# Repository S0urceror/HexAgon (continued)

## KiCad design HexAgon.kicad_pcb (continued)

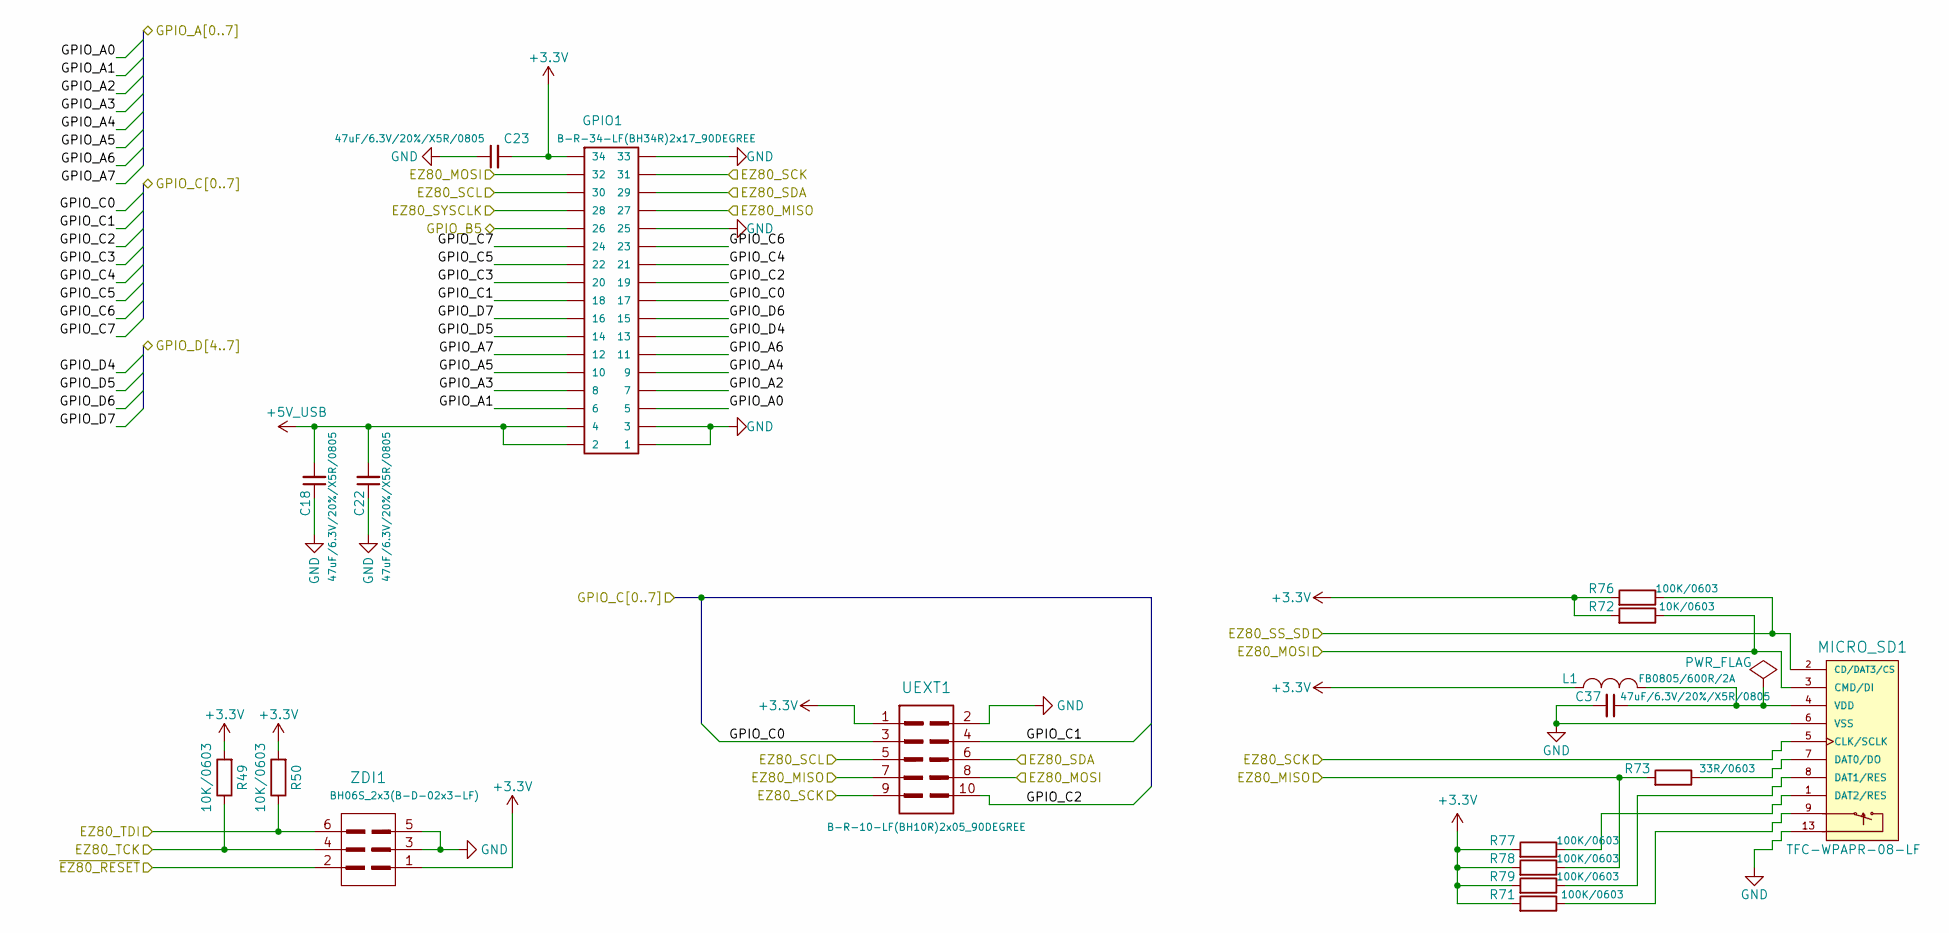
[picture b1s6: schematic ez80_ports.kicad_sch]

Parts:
C18, C22, C23, C37: 47uF/6.3V/20%/X5R/0805; C_0805_5MIL_DWS
GPIO1: B-R-34-LF(BH34R)2x17_90DEGREE; BH34R
L1: FB0805/600R/2A; L_0805_5MIL_DWS
MICRO_SD1: TFC-WPAPR-08-LF; TFC-WPAPR-08
R49, R50, R72: 10K/0603; R_0603_5MIL_DWS
R71, R76, R77, R78, R79: 100K/0603; R_0603_5MIL_DWS
R73: 33R/0603; R_0603_5MIL_DWS
UEXT1: B-R-10-LF(BH10R)2x05_90DEGREE; UEXT_BH10R
ZDI1: BH06S_2x3(B-D-02x3-LF); BH06S

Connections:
+3.3V: C23.2, GPIO1.34, L1.1, R49.2, R50.2, R71.2, R72.2, R76.2, R77.2, R78.2, R79.2, UEXT1.1, ZDI1.1; also elsewhere on the board
+5V_USB: C18.2, C22.2, GPIO1.2, GPIO1.4; also elsewhere on the board
/ESP32/ESP_SPI_MISO: GPIO1.27, R73.2, R78.1, UEXT1.7; also elsewhere on the board
/ESP32/ESP_SPI_MOSI: GPIO1.32, MICRO_SD1.3 (CMD/DI), R72.1, UEXT1.8; also elsewhere on the board
/ESP32/ESP_SPI_SCLK: GPIO1.31, MICRO_SD1.5 (CLK/SCLK), UEXT1.9; also elsewhere on the board
/EZ80 ports/EZ80_SCL: GPIO1.30, UEXT1.5; also elsewhere on the board
/EZ80 ports/EZ80_SDA: GPIO1.29, UEXT1.6; also elsewhere on the board
/EZ80 ports/EZ80_SS_SD: MICRO_SD1.2 (CD/DAT3/CS), R76.1; also elsewhere on the board
/EZ80 ports/EZ80_TCK: R49.1, ZDI1.4; also elsewhere on the board
/EZ80 ports/EZ80_TDI: R50.1, ZDI1.6; also elsewhere on the board
/EZ80 ports/GPIO_B5: GPIO1.26; also elsewhere on the board
/EZ80/CLOCK: GPIO1.28; also elsewhere on the board
/EZ80/PA0: GPIO1.5; also elsewhere on the board
/EZ80/PA1: GPIO1.6; also elsewhere on the board
/EZ80/PA2: GPIO1.7; also elsewhere on the board
/EZ80/PA3: GPIO1.8; also elsewhere on the board
/EZ80/PA4: GPIO1.9; also elsewhere on the board
/EZ80/PA5: GPIO1.10; also elsewhere on the board
/EZ80/PA6: GPIO1.11; also elsewhere on the board
/EZ80/PA7: GPIO1.12; also elsewhere on the board
/EZ80/PC0: GPIO1.17, UEXT1.3; also elsewhere on the board
/EZ80/PC1: GPIO1.18, UEXT1.4; also elsewhere on the board
/EZ80/PC2: GPIO1.19, UEXT1.10; also elsewhere on the board
/EZ80/PC3: GPIO1.20; also elsewhere on the board
/EZ80/PC4: GPIO1.21; also elsewhere on the board
/EZ80/PC5: GPIO1.22; also elsewhere on the board
/EZ80/PC6: GPIO1.23; also elsewhere on the board
/EZ80/PC7: GPIO1.24; also elsewhere on the board
/EZ80/PD4: GPIO1.13; also elsewhere on the board
/EZ80/PD5: GPIO1.14; also elsewhere on the board
/EZ80/PD6: GPIO1.15; also elsewhere on the board
/EZ80/PD7: GPIO1.16; also elsewhere on the board
/EZ80/~RESET: ZDI1.2; also elsewhere on the board
GND: C18.1, C22.1, C23.1, C37.2, GPIO1.1, GPIO1.3, GPIO1.25, GPIO1.33, MICRO_SD1.6 (VSS), MICRO_SD1.10, MICRO_SD1.11, MICRO_SD1.12, MICRO_SD1.13, UEXT1.2, ZDI1.3, ZDI1.5; also elsewhere on the board
unnamed: MICRO_SD1.7 (DAT0/DO), R73.1
unnamed: MICRO_SD1.8 (DAT1/RES), R79.1
unnamed: MICRO_SD1.1 (DAT2/RES), R77.1
unnamed: MICRO_SD1.9, R71.1
unnamed: C37.1, L1.2, MICRO_SD1.4 (VDD)

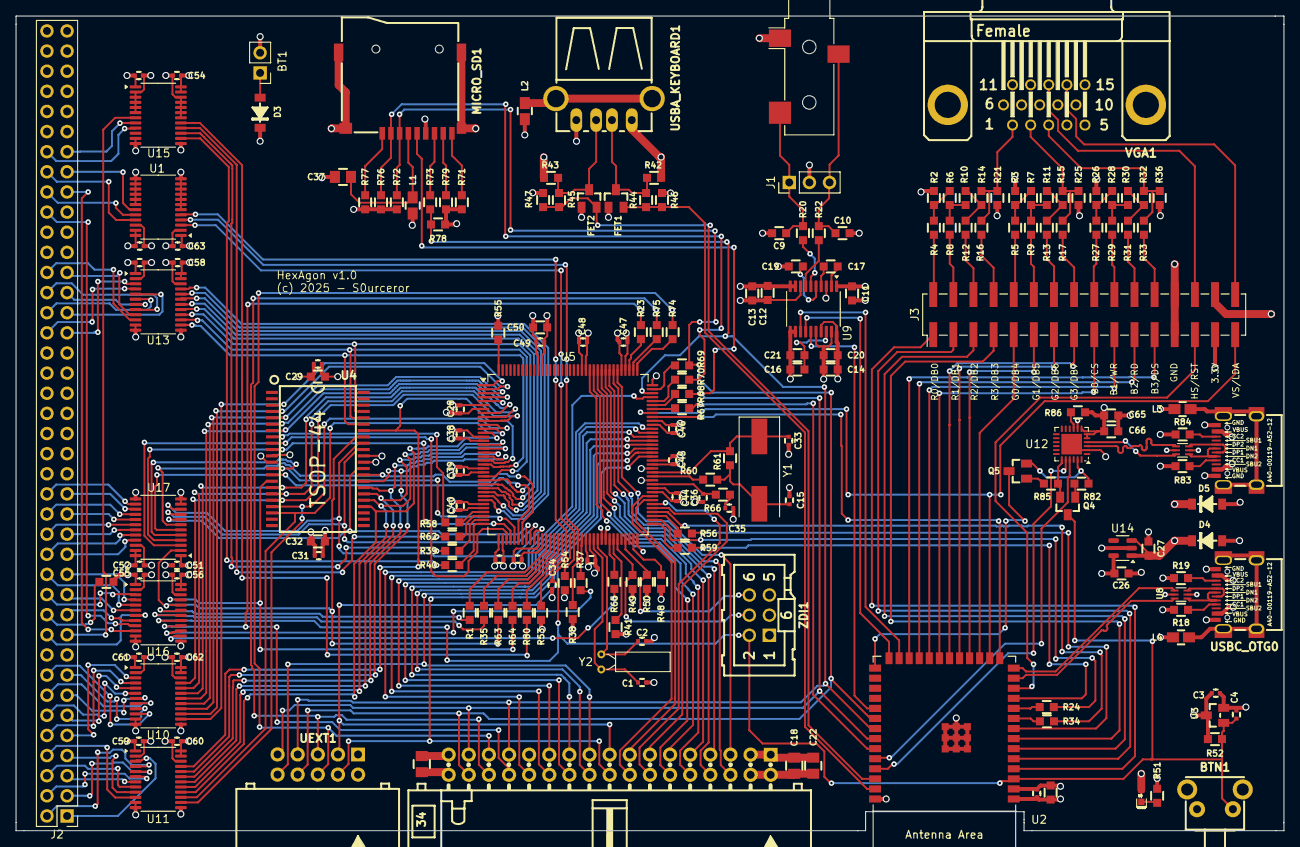
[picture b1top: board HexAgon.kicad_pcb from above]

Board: 4 copper layers, 160.0 x 102.8 mm, 191 parts (0 on the bottom side), 253 nets.

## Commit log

2024-11-05 initial setup
2025-05-10 schematics finished, pcb routing 80%
2025-05-18 v1.0 version PCB
2025-05-26 1st production and BOM
2025-05-26 hide mfgcodes from schematic
2025-06-08 PCB being built, recording errata
2025-08-17 fixed SD card issues
2025-08-24 all components tested, errata final
